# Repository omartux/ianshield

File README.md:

# Ian Labs Trainer
Shield Trainer para Arduino NANO

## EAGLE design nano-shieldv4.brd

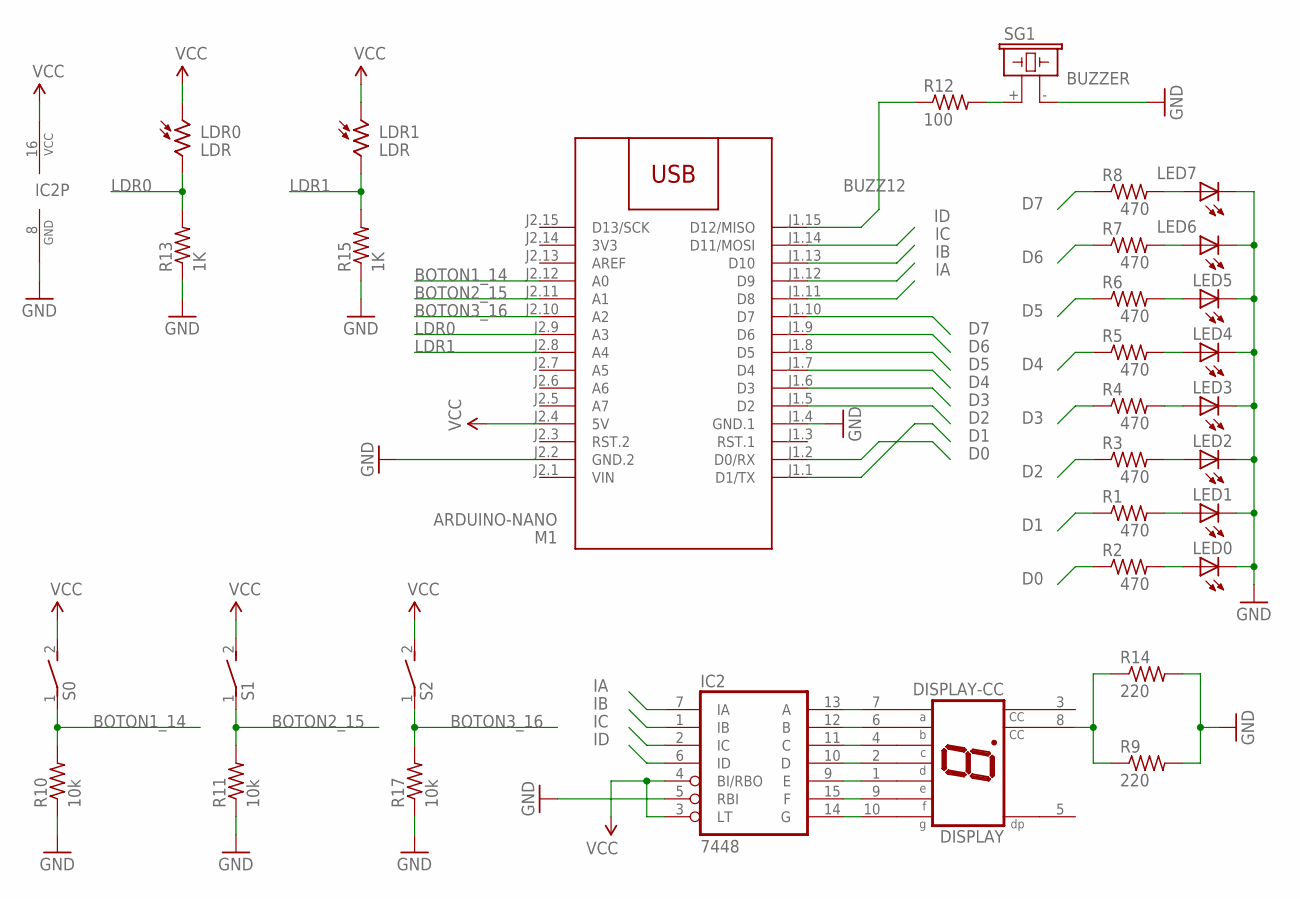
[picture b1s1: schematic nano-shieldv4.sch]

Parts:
DISPLAY: DISPLAY-CC; HDSP-M
IC2: 7448; DIL16
LDR0, LDR1: LDR; TO46-VT200
LED0, LED1, LED2, LED3, LED4, LED5, LED6, LED7: LED5MM
M1: ARDUINO-NANO; ARDUINO-NANO-3.0
R1, R2, R3, R4, R5, R6, R7, R8: 470; 0207/10
R9, R14: 220; 0207/10
R10, R11, R17: 10k; 0207/10
R12: 100; 0207/10
R13, R15: 1K; 0207/10
S0, S1, S2: DS01E; DS-01
SG1: BUZZER; F/CM12P

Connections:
3V3: M1.J2.14 (3V3)
BOTON1_14: M1.J2.12 (A0), R10.2, S0.1
BOTON2_15: M1.J2.11 (A1), R11.2, S1.1
BOTON3_16: M1.J2.10 (A2), R17.2, S2.1
BUZZ12: M1.J1.15 (D12/MISO), R12.1
D0: M1.J1.2 (D0/RX), R2.1
D1: M1.J1.1 (D1/TX), R1.1
D2: M1.J1.5 (D2), R3.1
D3: M1.J1.6 (D3), R4.1
D4: M1.J1.7 (D4), R5.1
D5: M1.J1.8 (D5), R6.1
D6: M1.J1.9 (D6), R7.1
D7: M1.J1.10 (D7), R8.1
GND: IC2.5 (RBI), IC2.8 (GND), LED0.K (C), LED1.K (C), LED2.K (C), LED3.K (C), LED4.K (C), LED5.K (C), LED6.K (C), LED7.K (C), M1.J1.4 (GND.1), M1.J2.2 (GND.2), R9.2, R10.1, R11.1, R13.1, R14.2, R15.1, R17.1, SG1.- (2)
IA: IC2.7 (IA), M1.J1.11 (D8)
IB: IC2.1 (IB), M1.J1.12 (D9)
IC: IC2.2 (IC), M1.J1.13 (D10)
ID: IC2.6 (ID), M1.J1.14 (D11/MOSI)
LDR0: LDR0.2, M1.J2.9 (A3), R13.2
LDR1: LDR1.2, M1.J2.8 (A4), R15.2
unnamed: R12.2, SG1.+ (1)
unnamed: LED0.A, R2.2
unnamed: LED1.A, R1.2
unnamed: LED2.A, R3.2
unnamed: LED3.A, R4.2
unnamed: LED4.A, R5.2
unnamed: LED5.A, R6.2
unnamed: LED6.A, R7.2
unnamed: LED7.A, R8.2
unnamed: DISPLAY.1 (E), IC2.9 (E)
unnamed: DISPLAY.2 (D), IC2.10 (D)
unnamed: DISPLAY.4 (C), IC2.11 (C)
unnamed: DISPLAY.6 (B), IC2.12 (B)
unnamed: DISPLAY.7 (A), IC2.13 (A)
unnamed: DISPLAY.10 (G), IC2.14 (G)
unnamed: DISPLAY.9 (F), IC2.15 (F)
unnamed: DISPLAY.8 (CC), R9.1, R14.1
VCC: IC2.3 (LT), IC2.4 (BI/RBO), IC2.16 (VCC), LDR0.1, LDR1.1, M1.J2.4 (5V), S0.2, S1.2, S2.2
VIN: M1.J2.1 (VIN)

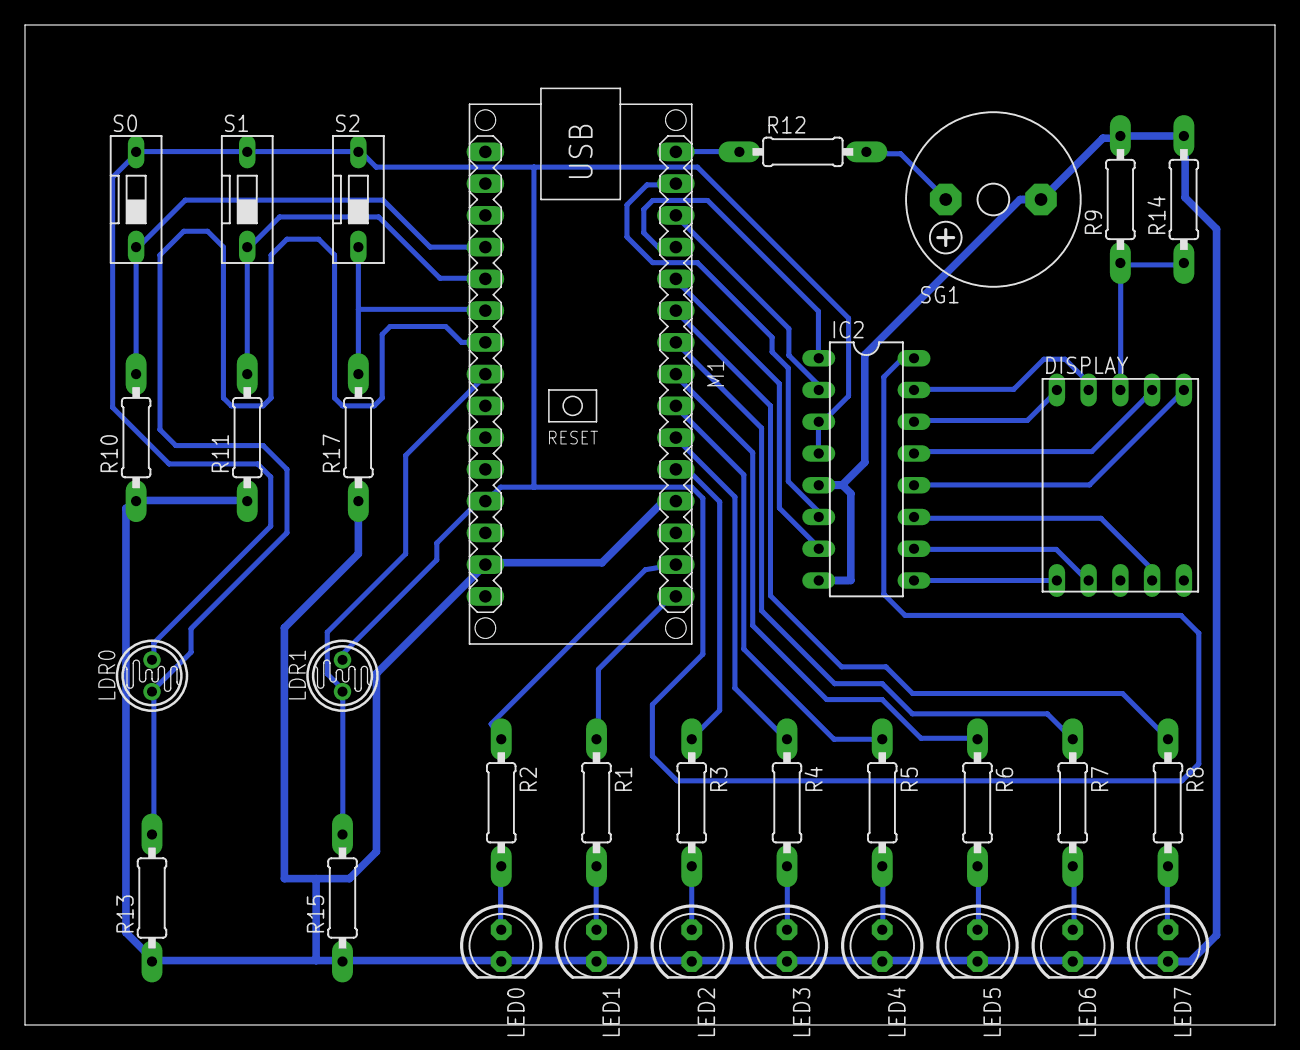
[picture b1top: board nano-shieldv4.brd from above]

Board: 2 copper layers, 100.0 x 80.0 mm, 33 parts (0 on the bottom side), 37 nets.

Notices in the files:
parts and their libraries:
diy-modules: Released under the Creative Commons Attribution 4.0 International License: http://creativecommons.org/licenses/by/4.0
SparkFun-Aesthetics: Licensing: Creative Commons ShareAlike 4.0 International - https://creativecommons.org/licenses/by-sa/4.0
